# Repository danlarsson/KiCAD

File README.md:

# KiCAD Projeckts
Some random electronic projects created with KiCAD. 

## Piezo Amplifier
A mono microphone Amplifier for Piezo Microphones.

- [X] Designed
- [X] Ordered
- [] Built
- [] Tested

## Pi-Shield / SSR-Shield
The SSR Shield is used instead of a realay to control a load on mac 24 Volt 2 Ampere with a Raspberry Pi

- [X] Designed
- [X] Ordered
- [X] Built
- [X] Tested

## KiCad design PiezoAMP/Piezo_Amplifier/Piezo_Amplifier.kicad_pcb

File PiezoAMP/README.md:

# Piezo Amplifier
A mono microphone Amplifier for Piezo Microphones.

The design is borrows from Richard Mudhar, who has a nice description with exampels on his blog
https://www.richardmudhar.com/blog/piezo-contact-microphone-hi-z-amplifier-low-noise-version/

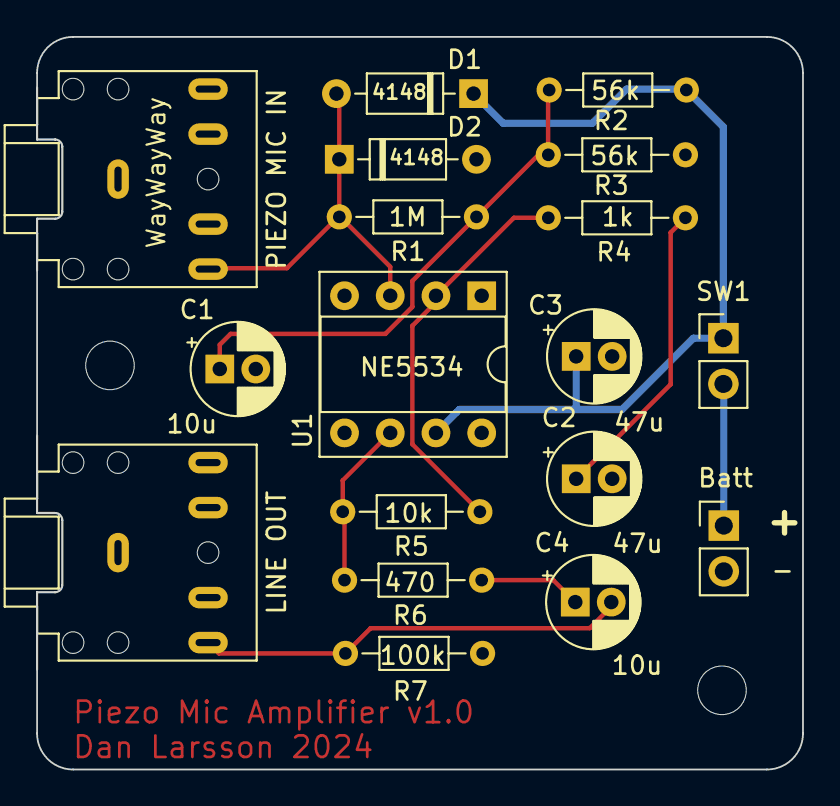
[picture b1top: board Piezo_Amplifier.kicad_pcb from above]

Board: 2 copper layers, 42.5 x 40.7 mm, 18 parts (0 on the bottom side), 10 nets.

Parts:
Batt: 9V; PinHeader_1x02_P2.54mm_Vertical
C1, C4: 10u; CP_Radial_D5.0mm_P2.00mm
C2, C3: 47u; CP_Radial_D5.0mm_P2.00mm
D1, D2: 4148; D_DO-35_SOD27_P7.62mm_Horizontal
LINE OUT: Audio Out; Jack_3.5mm_CUI_SJ1-3525N_Horizontal
PIEZO MIC IN: Piezo Mic; Jack_3.5mm_CUI_SJ1-3525N_Horizontal
R1: 1M; R_Axial_DIN0204_L3.6mm_D1.6mm_P7.62mm_Horizontal
R2, R3: 56k; R_Axial_DIN0204_L3.6mm_D1.6mm_P7.62mm_Horizontal
R4: 1k; R_Axial_DIN0204_L3.6mm_D1.6mm_P7.62mm_Horizontal
R5: 10k; R_Axial_DIN0204_L3.6mm_D1.6mm_P7.62mm_Horizontal
R6: 470; R_Axial_DIN0204_L3.6mm_D1.6mm_P7.62mm_Horizontal
R7: 100k; R_Axial_DIN0204_L3.6mm_D1.6mm_P7.62mm_Horizontal
SW1: SPST; PinHeader_1x02_P2.54mm_Vertical
U1: NE5534; DIP-8_W7.62mm_Socket

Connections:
/VCC: C3.1, D1.1 (K), R2.1, SW1.1 (A), U1.7 (V+)
GND: Batt.2 (-), C1.2, C2.2, C3.2, D2.2 (A), LINE OUT.S, PIEZO MIC IN.S, R3.2, R7.2, U1.4 (V-)
unnamed: Batt.1 (+), SW1.2 (B)
unnamed: C1.1, R1.1, R2.2, R3.1
unnamed: C2.1, R4.2
unnamed: C4.1, R6.2
unnamed: C4.2, LINE OUT.T, R7.1
unnamed: D1.2 (A), D2.1 (K), PIEZO MIC IN.T, R1.2, U1.3 (+)
unnamed: R5.2, R6.1, U1.6
unnamed: R4.1, R5.1, U1.2 (-)

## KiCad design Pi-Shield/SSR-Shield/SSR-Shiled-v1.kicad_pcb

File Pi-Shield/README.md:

# Solid State Relay

Raspery Pi Shiled with two Solid State Relays and a button.
Can be used to control voltages around 24V 2A.

Panasonic AQZ202D 60V 2.7A  - Divs med 1.4V - 4V, 6.4mA
- https://www.mouser.se/ProductDetail/Panasonic-Industrial-Devices/AQZ202D?qs=wKtUvITRiamx%252B1RZTBBykA%3D%3D
- https://www.mouser.se/datasheet/2/315/Panasonic_080420_AQZ-1889739.pdf

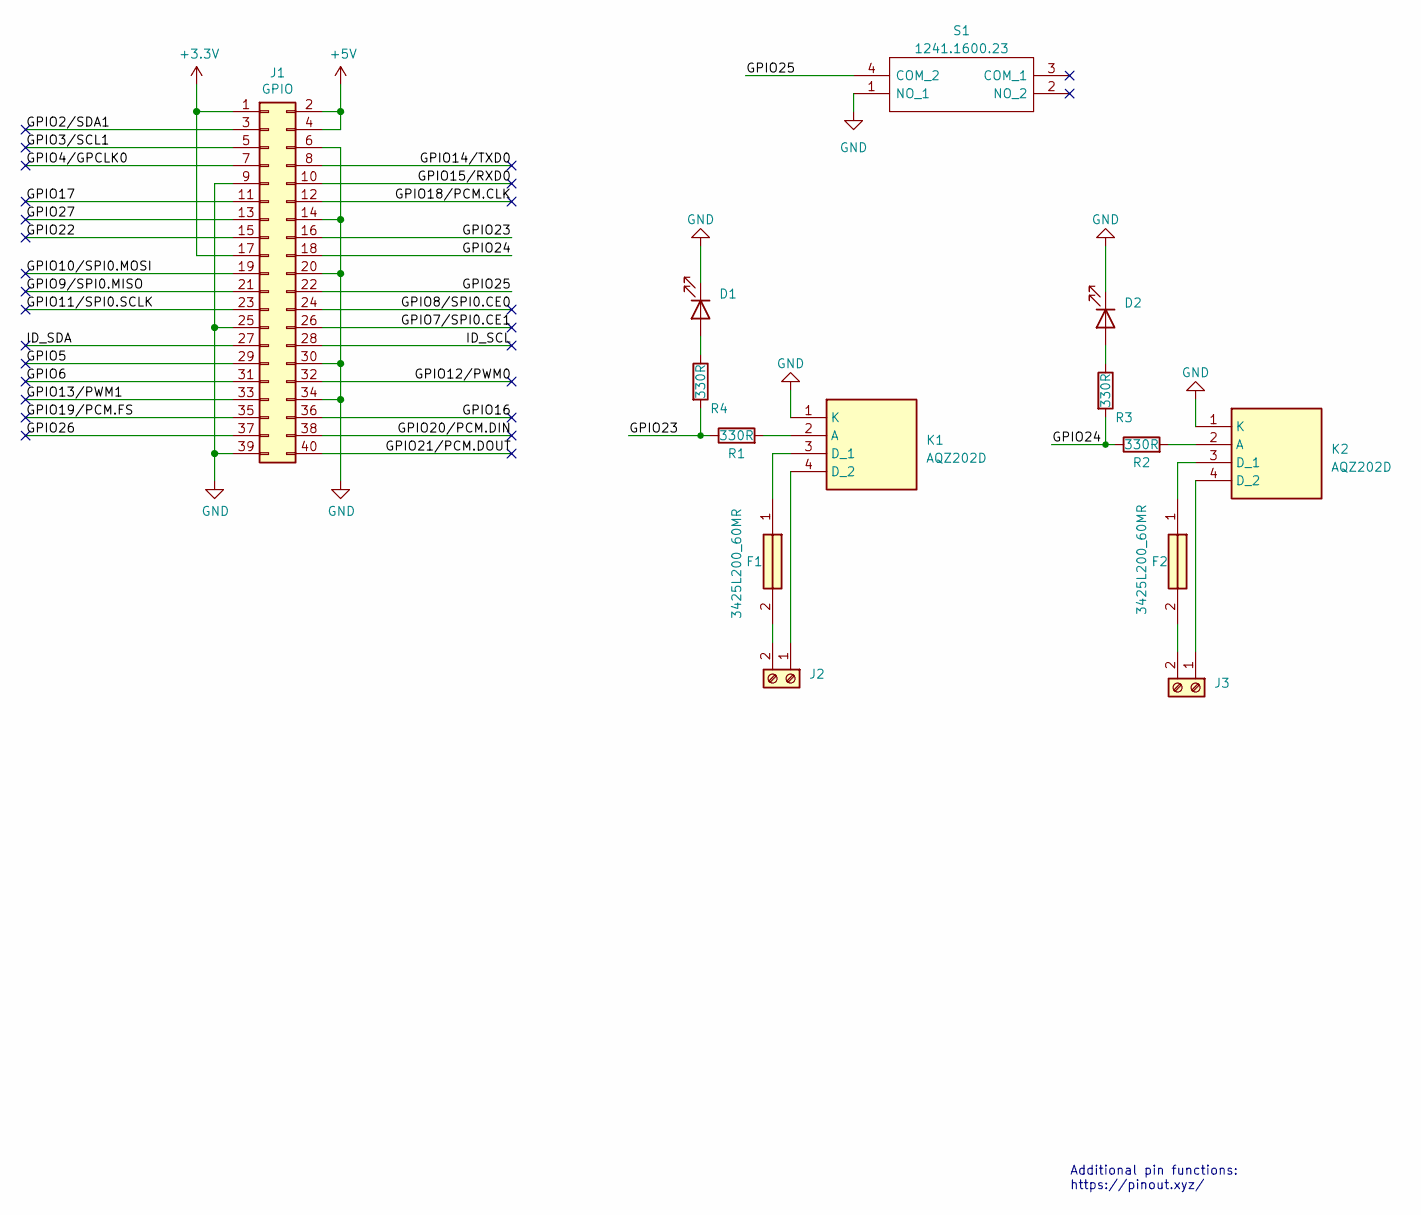
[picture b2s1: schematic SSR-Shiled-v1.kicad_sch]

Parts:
D1, D2: IR26-21C_L110_TR8; LED_1206_3216Metric
F1, F2: 3425L200_60MR; FUSC8664X180N; Mouser Part Number 576-3425L200/60MR
J1: GPIO; PinSocket_2x20_P2.54mm_Vertical
J2, J3: Screw_Terminal_01x02; TerminalBlock_Phoenix_PT-1,5-2-5.0-H_1x02_P5.00mm_Horizontal
K1, K2: AQZ202D; AQZ202G; Mouser Part Number 769-AQZ202D
R1, R2, R3, R4: 330R; R_1206_3216Metric
S1: 1241.1600.23; 1241160023; Mouser Part Number 693-1241.1600.23

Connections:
+3V3: J1.1, J1.17
+5V: J1.2, J1.4
/GPIO2/SDA1: J1.3
/GPIO3/SCL1: J1.5
/GPIO4/GPCLK0: J1.7
/GPIO5: J1.29
/GPIO6: J1.31
/GPIO7/SPI0.CE1: J1.26
/GPIO8/SPI0.CE0: J1.24
/GPIO9/SPI0.MISO: J1.21
/GPIO10/SPI0.MOSI: J1.19
/GPIO11/SPI0.SCLK: J1.23
/GPIO12/PWM0: J1.32
/GPIO13/PWM1: J1.33
/GPIO14/TXD0: J1.8
/GPIO15/RXD0: J1.10
/GPIO16: J1.36
/GPIO17: J1.11
/GPIO18/PCM.CLK: J1.12
/GPIO19/PCM.FS: J1.35
/GPIO20/PCM.DIN: J1.38
/GPIO21/PCM.DOUT: J1.40
/GPIO22: J1.15
/GPIO23: J1.16, R1.1, R4.2
/GPIO24: J1.18, R2.1, R3.2
/GPIO25: J1.22, S1.4 (COM_2)
/GPIO26: J1.37
/GPIO27: J1.13
/ID_SCL: J1.28
/ID_SDA: J1.27
GND: D1.1 (K), D2.1 (K), J1.6, J1.9, J1.14, J1.20, J1.25, J1.30, J1.34, J1.39, K1.1 (K), K2.1 (K), S1.1 (NO_1)
unnamed: D1.2 (A), R4.1
unnamed: D2.2 (A), R3.1
unnamed: J2.1, K1.4 (D_2)
unnamed: F1.2, J2.2
unnamed: J3.1, K2.4 (D_2)
unnamed: F2.2, J3.2
unnamed: K1.2 (A), R1.2
unnamed: F1.1, K1.3 (D_1)
unnamed: K2.2 (A), R2.2
unnamed: F2.1, K2.3 (D_1)

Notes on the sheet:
Additional pin functions: https://pinout.xyz/

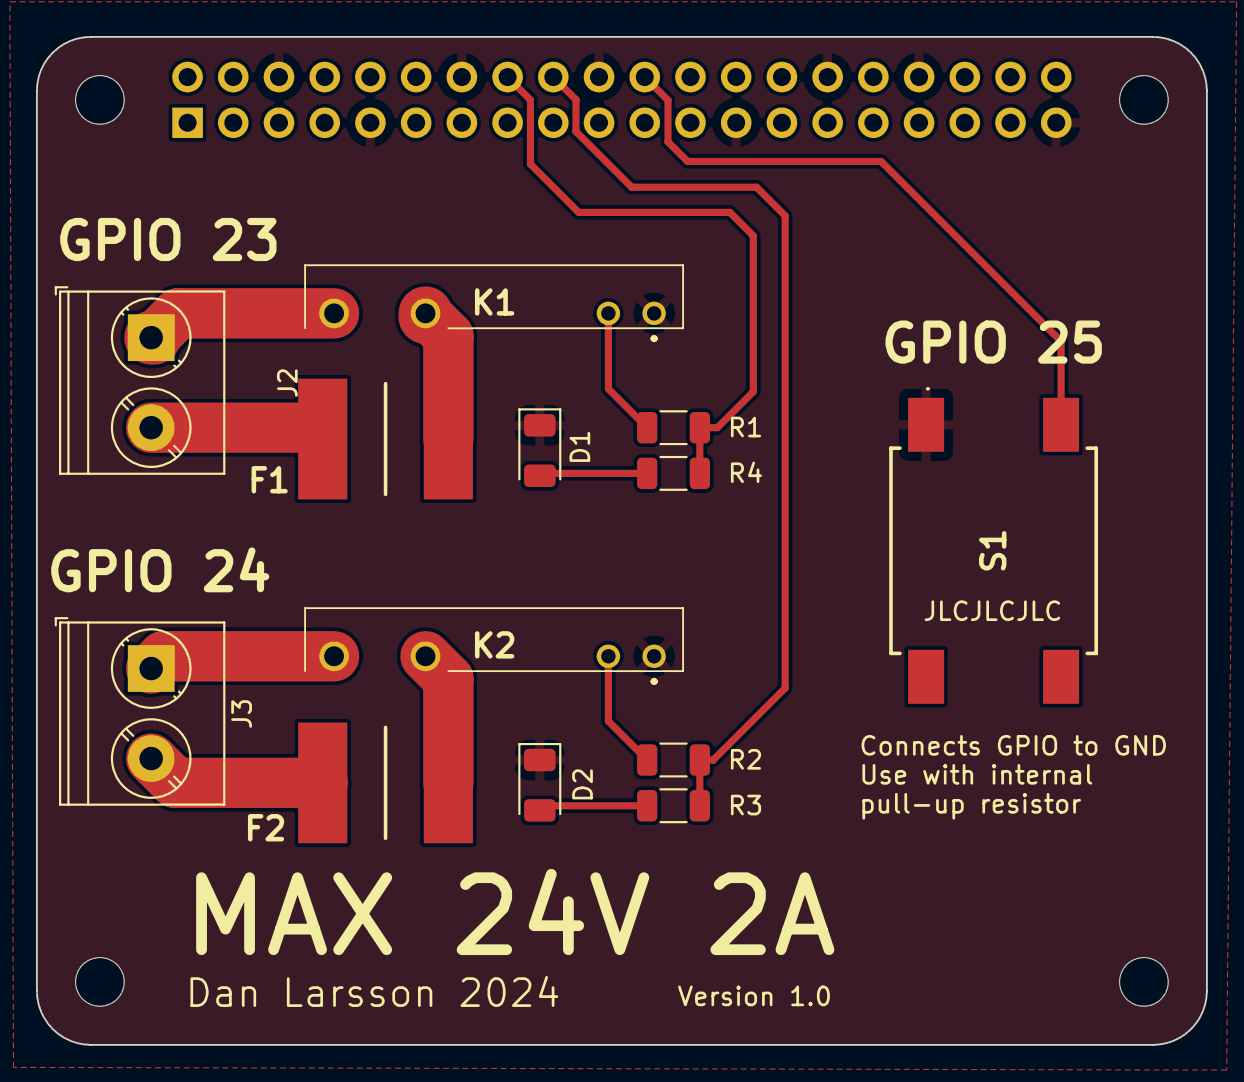
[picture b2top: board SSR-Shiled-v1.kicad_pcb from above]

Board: 2 copper layers, 65.0 x 56.0 mm, 18 parts (1 on the bottom side), 16 nets.

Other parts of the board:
MH1, MH2, MH3, MH4: MountingHole_2.7mm_M2.5

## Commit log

2024-12-13 Cleanup
